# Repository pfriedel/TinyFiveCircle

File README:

Requirements:

1) 5 RGB LEDs - I'm using common anode, but it'll work with common cathode.
   Just differently.  You'll have to map out the pins and colors differently.

2) ATtiny85

3) PCB from OSHpark.  I'm working on a kit.

BOM: (prices are volatile)

1x MCU: http://www.dipmicro.com/store/ATTINY85-20PU ($1.56)
4x 10mm RGB Common Anode LEDs: http://www.dipmicro.com/store/LED10AD ($2)
1x 3xAA Battery holder: http://www.dipmicro.com/store/BH2465 ($3.21)
4x resistors - mine are 1ohm! But 47 is probably more reasonable

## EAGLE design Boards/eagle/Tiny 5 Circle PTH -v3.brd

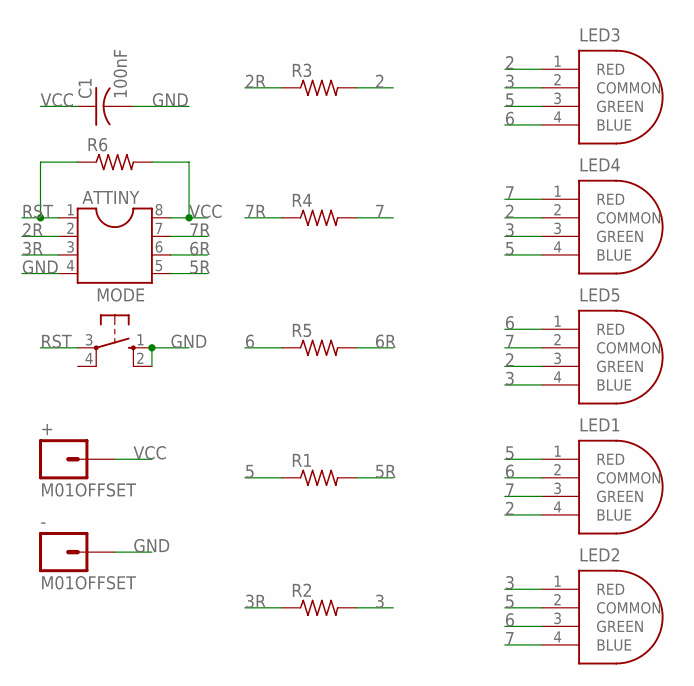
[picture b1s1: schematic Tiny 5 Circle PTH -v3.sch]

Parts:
+: M01OFFSET; 1X01_OFFSET
-: M01OFFSET; 1X01_OFFSET
ATTINY: DIL8S; SOCKET-08
C1: 100nF; C025-025X050
LED1, LED2, LED3, LED4, LED5: 10MM-RGB-LEDACTIVELYUSED; 10MM-RGB-LED-IN-USE
MODE: 10-XX; B3F-10XX
R1, R2, R3, R4, R5: R-US_0207/7; 0207/7
R6: R-US_0207/2V; 0207/2V

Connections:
2: LED1.4 (BLUE), LED3.1 (RED), LED4.2 (COMMON), LED5.3 (GREEN), R3.2
2R: ATTINY.2, R3.1
3: LED2.1 (RED), LED3.2 (COMMON), LED4.3 (GREEN), LED5.4 (BLUE), R2.2
3R: ATTINY.3, R2.1
5: LED1.1 (RED), LED2.2 (COMMON), LED3.3 (GREEN), LED4.4 (BLUE), R1.1
5R: ATTINY.5, R1.2
6: LED1.2 (COMMON), LED2.3 (GREEN), LED3.4 (BLUE), LED5.1 (RED), R5.1
6R: ATTINY.6, R5.2
7: LED1.3 (GREEN), LED2.4 (BLUE), LED4.1 (RED), LED5.2 (COMMON), R4.2
7R: ATTINY.7, R4.1
GND: -.1, ATTINY.4, C1.2, MODE.1 (S), MODE.2 (S1)
RST: ATTINY.1, MODE.3, R6.1
VCC: +.1, ATTINY.8, C1.1, R6.2

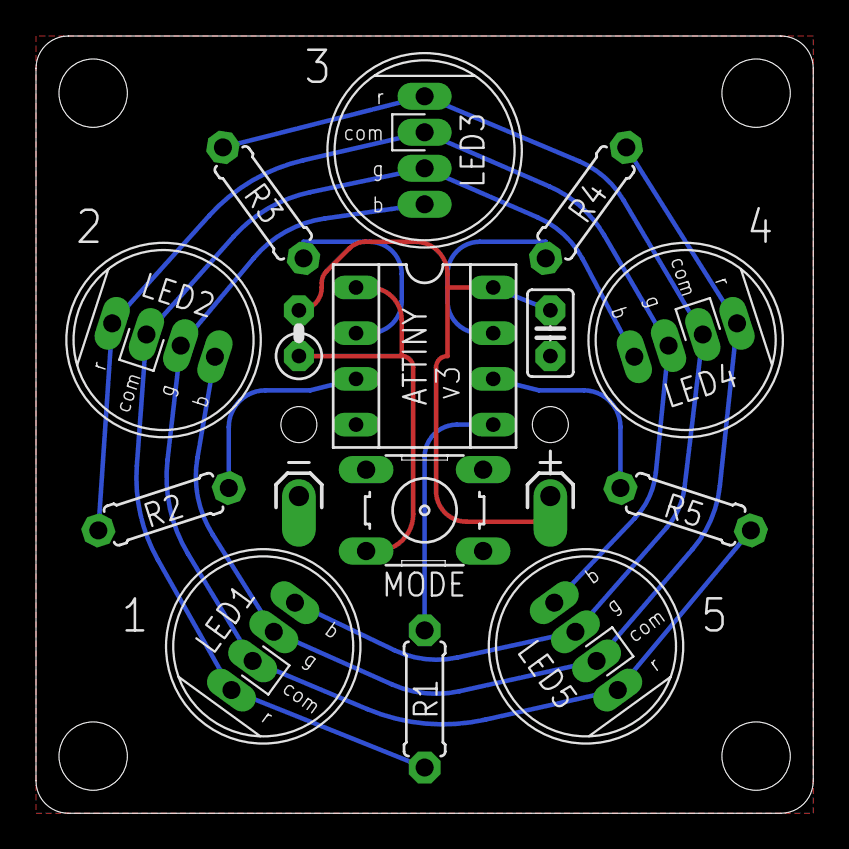
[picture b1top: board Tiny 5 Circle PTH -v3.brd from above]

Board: 2 copper layers, 43.2 x 43.2 mm, 16 parts (0 on the bottom side), 13 nets.

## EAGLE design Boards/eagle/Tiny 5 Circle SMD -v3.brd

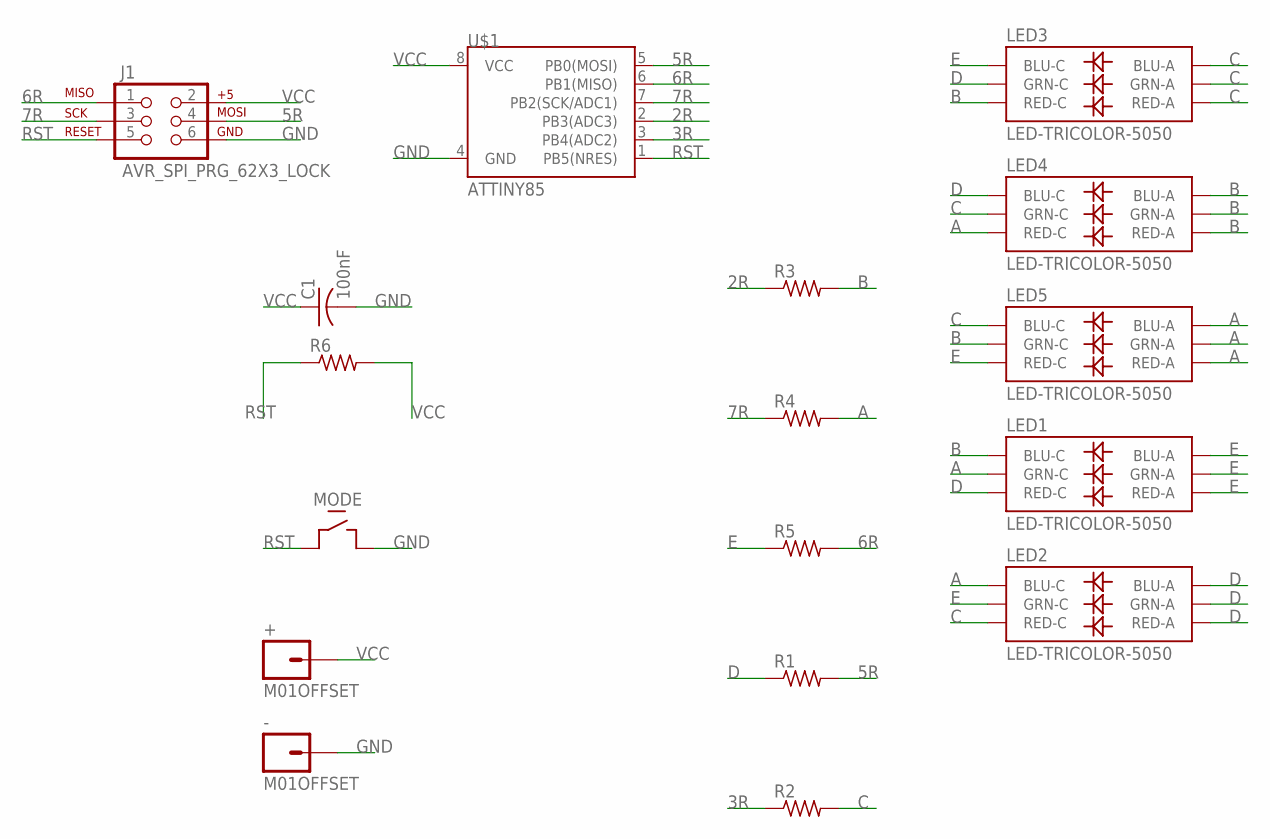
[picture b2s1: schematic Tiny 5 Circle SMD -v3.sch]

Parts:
+: M01OFFSET; 1X01_OFFSET
-: M01OFFSET; 1X01_OFFSET
C1: 100nF; C025-025X050
J1: AVR_SPI_PRG_62X3_LOCK; 2X3_LOCK
LED1, LED2, LED3, LED4, LED5: LED-TRICOLOR-5050
MODE: 3X6MM_SWITCH; 6X3MM-TACT
R1, R2, R3, R4, R5, R6: R-US_M0805; M0805
U$1: ATTINY85; SO08-EIAJ

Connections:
2R: R3.1, U$1.2 (PB3(ADC3))
3R: R2.1, U$1.3 (PB4(ADC2))
5R: J1.4, R1.2, U$1.5 (PB0(MOSI))
6R: J1.1, R5.2, U$1.6 (PB1(MISO))
7R: J1.3, R4.1, U$1.7 (PB2(SCK/ADC1))
A: LED1.4 (GRN-C), LED2.6 (BLU-C), LED4.5 (RED-C), LED5.1 (BLU-A), LED5.2 (RED-A), LED5.3 (GRN-A), R4.2
B: LED1.6 (BLU-C), LED3.5 (RED-C), LED4.1 (BLU-A), LED4.2 (RED-A), LED4.3 (GRN-A), LED5.4 (GRN-C), R3.2
C: LED2.5 (RED-C), LED3.1 (BLU-A), LED3.2 (RED-A), LED3.3 (GRN-A), LED4.4 (GRN-C), LED5.6 (BLU-C), R2.2
D: LED1.5 (RED-C), LED2.1 (BLU-A), LED2.2 (RED-A), LED2.3 (GRN-A), LED3.4 (GRN-C), LED4.6 (BLU-C), R1.1
E: LED1.1 (BLU-A), LED1.2 (RED-A), LED1.3 (GRN-A), LED2.4 (GRN-C), LED3.6 (BLU-C), LED5.5 (RED-C), R5.1
GND: -.1, C1.2, J1.6, MODE.P$2 (OUT), U$1.4 (GND)
RST: J1.5, MODE.P$1 (IN), R6.1, U$1.1 (PB5(NRES))
VCC: +.1, C1.1, J1.2, R6.2, U$1.8 (VCC)

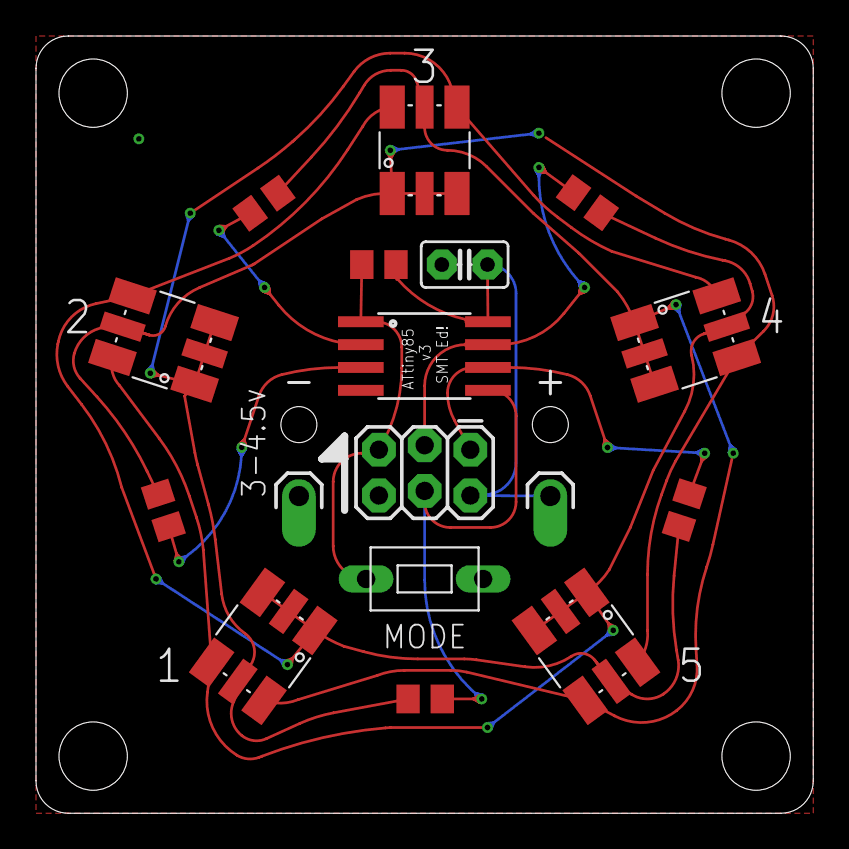
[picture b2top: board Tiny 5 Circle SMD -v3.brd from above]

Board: 2 copper layers, 43.2 x 43.2 mm, 17 parts (0 on the bottom side), 13 nets.

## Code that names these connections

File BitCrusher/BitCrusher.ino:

// Because I tend to forget - the number here is the Port B pin in use.  Pin 5 is PB0, Pin 6 is PB1, etc.
#define LINE_A 0 // PB0 / Pin 5 on ATtiny85 / Pin 14 on an ATmega328 (D8)
#define LINE_B 1 // PB1 / Pin 6 on ATtiny85 / Pin 15 on an ATmega328 (D9)
#define LINE_C 2 // PB2 / Pin 7 on ATtiny85 / Pin 17 on an ATmega328 (D11)
#define LINE_D 3 // PB3 / Pin 2 on ATtiny85 / Pin 18 on an ATmega328 (D12)
#define LINE_E 4 // PB4 / Pin 3 on ATtiny85

#include <avr/power.h>
#include <EEPROM.h>

// How many modes do we want to go through?
#define MAX_MODE 9
// How long should I draw each color on each LED?
#define DRAW_TIME 5

// Location of the brown-out disable switch in the MCU Control Register (MCUCR)
#define BODS 7 
// Location of the Brown-out disable switch enable bit in the MCU Control Register (MCUCR)
#define BODSE 2 

// The base unit for the time comparison. 1000=1s, 10000=10s, 60000=1m, etc.
//#define time_multiplier 1000 
#define time_multiplier 60000
// How many time_multiplier intervals should run before going to sleep?
#define run_time 240

#define MAX_HUE 360 // normalized

// How bit-crushed do you want the bit depth to be?  1 << TIMESCALE is how
// quickly it goes through the LED softpwm scale.

// 1 means 128 shades per color.  3 is 32 colors while 6 is 4 shades per color.
// it sort of scales the time drawing routine, but not well.

// It also affects how bright it it (less time spent drawing nothing) as well as
// the POV flickering rate. Higher numbers are both brighter and less flicker-y.

// the build uses 1 for the PTH versions and 3 for the SMD displays.

#define TIMESCALE 3

byte __attribute__ ((section (".noinit"))) last_mode;

uint8_t led_grid[15] = {
  000 , 000 , 000 , 000 , 000 , // R
  000 , 000 , 000 , 000 , 000 , // G
  000 , 000 , 000 , 000 , 000  // B
};

uint8_t led_grid_next[15] = {
  000 , 000 , 000 , 000 , 000 , // R
  000 , 000 , 000 , 000 , 000 , // G
  000 , 000 , 000 , 000 , 000  // B
};


void setup() {
  Serial.begin(115200);
}

void loop() {
  HueWalk(run_time,millis(),5,1); // 1:1 space to LED, fast progression
}

void HueWalk(uint16_t time, uint32_t start_time, uint8_t width, uint8_t speed) {
  while(1) {
    
    if(millis() >= (start_time + (time * time_multiplier))) { break; }

    for(int16_t colorshift=MAX_HUE; colorshift>0; colorshift = colorshift - speed) {

      if(millis() >= (start_time + (time * time_multiplier))) { break; }
      for(uint8_t led = 0; led<5; led++) {
	//	if(led == 0) { Serial.println(colorshift); }

	uint16_t hue = ((led) * MAX_HUE/(width)+colorshift)%MAX_HUE;
	setLedColorHSV(led, hue, 255, 255);
      }
      draw_for_time(DRAW_TIME); // this gets called 5 times, once per LED.
    }
  }
}


const byte dim_curve[] = {
  0,   1,   1,   2,   2,   2,   2,   2,   2,   3,   3,   3,   3,   3,   3,   3,
  3,   3,   3,   3,   3,   3,   3,   4,   4,   4,   4,   4,   4,   4,   4,   4,
  4,   4,   4,   5,   5,   5,   5,   5,   5,   5,   5,   5,   5,   6,   6,   6,
  6,   6,   6,   6,   6,   7,   7,   7,   7,   7,   7,   7,   8,   8,   8,   8,
  8,   8,   9,   9,   9,   9,   9,   9,   10,  10,  10,  10,  10,  11,  11,  11,
  11,  11,  12,  12,  12,  12,  12,  13,  13,  13,  13,  14,  14,  14,  14,  15,
  15,  15,  16,  16,  16,  16,  17,  17,  17,  18,  18,  18,  19,  19,  19,  20,
  20,  20,  21,  21,  22,  22,  22,  23,  23,  24,  24,  25,  25,  25,  26,  26,
  27,  27,  28,  28,  29,  29,  30,  30,  31,  32,  32,  33,  33,  34,  35,  35,
  36,  36,  37,  38,  38,  39,  40,  40,  41,  42,  43,  43,  44,  45,  46,  47,
  48,  48,  49,  50,  51,  52,  53,  54,  55,  56,  57,  58,  59,  60,  61,  62,
  63,  64,  65,  66,  68,  69,  70,  71,  73,  74,  75,  76,  78,  79,  81,  82,
  83,  85,  86,  88,  90,  91,  93,  94,  96,  98,  99,  101, 103, 105, 107, 109,
  110, 112, 114, 116, 118, 121, 123, 125, 127, 129, 132, 134, 136, 139, 141, 144,
  146, 149, 151, 154, 157, 159, 162, 165, 168, 171, 174, 177, 180, 183, 186, 190,
  193, 196, 200, 203, 207, 211, 214, 218, 222, 226, 230, 234, 238, 242, 248, 255,
};


/*
Inputs:
  p : LED to set
  immediate : Whether the change should go to led_grid or led_grid_next
  hue : 0-360 - color
  sat : 0-255 - how saturated should it be? 0=white, 255=full color
  val : 0-255 - how bright should it be? 0=off, 255=full bright
*/
void setLedColorHSV(uint8_t p, int16_t hue, int16_t sat, int16_t val) {


  /*
    so dim_curve duplicates too many of the low numbers too long, causing the
    animations to look janky.  Maybe 6 2's and 14 3's can be adjusted in other ways.
    
    val = dim_curve[val];
    sat = 255-dim_curve[255-sat];
  */

  while (hue > 360) hue -= 361;
  while (hue < 0) hue += 361;

  int r, g, b, base;

  if (sat == 0) { // Acromatic color (gray). Hue doesn't mind.
    r = g = b = val;
  }
  else {
    base = ((255 - sat) * val)>>8;

    switch(hue/60) {
    case 0:
      r = val;
      g = (((val-base)*hue)/60)+base;
      b = base;
      break;

    case 1:
      r = (((val-base)*(60-(hue%60)))/60)+base;
      g = val;
      b = base;
      break;

    case 2:
      r = base;
      g = val;
      b = (((val-base)*(hue%60))/60)+base;
      break;

    case 3:
      r = base;
      g = (((val-base)*(60-(hue%60)))/60)+base;
      b = val;
      break;

    case 4:
      r = (((val-base)*(hue%60))/60)+base;
      g = base;
      b = val;
      break;

    case 5:
      r = val;
      g = base;
      b = (((val-base)*(60-(hue%60)))/60)+base;
      break;
    }
  }

  // output range is 0-255

  r = r>>TIMESCALE;
  g = g>>TIMESCALE;
  b = b>>TIMESCALE;

  if(p == 0) { 
    Serial.print(hue); 
    Serial.print("  r: "); Serial.print(r);
    Serial.print(" g: "); Serial.print(g);
    Serial.print(" b: "); Serial.println(b);
    
  }


  set_led_rgb(p,r,g,b);
}

/* Args:
   position - 0-4
   red value - 0-255
   green value - 0-255
   blue value - 0-255
*/
void set_led_rgb (uint8_t p, uint8_t r, uint8_t g, uint8_t b) {
  led_grid[p] = r;
  led_grid[p+5] = g;
  led_grid[p+10] = b;
}

// runs draw_frame a supplied number of times.
void draw_for_time(uint16_t time) {
  Serial.print("BEGINNING draw_for_time for ");
  Serial.print(time * (1<<(TIMESCALE-1)));
  Serial.println(" loops.");
  
  for(uint16_t f = 0; f<time * (1 << (TIMESCALE-1)); f++) { 
    draw_frame();   
  }
  Serial.println("ENDING draw_for_time");
  
}

// Anode | cathode
const uint8_t led_dir[15] = {
  ( 1<<LINE_B | 1<<LINE_A ), // 4 r
  ( 1<<LINE_A | 1<<LINE_E ), // 5 r
  ( 1<<LINE_E | 1<<LINE_D ), // 1 r
  ( 1<<LINE_D | 1<<LINE_C ), // 2 r
  ( 1<<LINE_C | 1<<LINE_B ), // 3 r

  ( 1<<LINE_B | 1<<LINE_C ), // 4 g
  ( 1<<LINE_A | 1<<LINE_B ), // 5 g
  ( 1<<LINE_E | 1<<LINE_A ), // 1 g
  ( 1<<LINE_D | 1<<LINE_E ), // 2 g
  ( 1<<LINE_C | 1<<LINE_D ), // 3 g

  ( 1<<LINE_B | 1<<LINE_D ), // 4 b
  ( 1<<LINE_A | 1<<LINE_C ), // 5 b
  ( 1<<LINE_E | 1<<LINE_B ), // 1 b
  ( 1<<LINE_D | 1<<LINE_A ), // 2 b
  ( 1<<LINE_C | 1<<LINE_E ), // 3 b
};

//PORTB output config for each LED (1 = High, 0 = Low)
const uint8_t led_out[15] = {
  ( 1<<LINE_B ), // 4 r
  ( 1<<LINE_A ), // 5 r
  ( 1<<LINE_E ), // 1 r
  ( 1<<LINE_D ), // 2 r
  ( 1<<LINE_C ), // 3 r
  
  ( 1<<LINE_B ), // 4 g
  ( 1<<LINE_A ), // 5 g
  ( 1<<LINE_E ), // 1 g
  ( 1<<LINE_D ), // 2 g
  ( 1<<LINE_C ), // 3 g
  
  ( 1<<LINE_B ), // 4 b
  ( 1<<LINE_A ), // 5 b
  ( 1<<LINE_E ), // 1 b
  ( 1<<LINE_D ), // 2 b
  ( 1<<LINE_C ), // 3 b
};

void light_led(uint8_t led_num) { //led_num must be from 0 to 19
  //DDRD is the ports in use on an ATmega328, DDRB on an ATtiny85
  DDRB = led_dir[led_num];
  PORTB = led_out[led_num];
}

void leds_off() {
  DDRB = 0;
  PORTB = 0;
}

void draw_frame(void){
  uint16_t b;
  uint8_t led;
  // giving the loop a bit of breathing room seems to prevent the last LED from flickering.  Probably optimizes into oblivion anyway.
  for ( led=0; led<=15; led++ ) { 

    for( b=0; b<led_grid[led]; b++) {
      light_led(led);
      if(led == 0) {
	Serial.print(1);
      }
    }
    // and turn the LEDs off for the amount of time in the led_grid array between LED brightness and 255.
    // BUG alert - at timescale 3, 
    // input "68" is 33 total cycles, 9 lit and 24 dark, 
    // input "63" is 32 total cycles, 8 lit and 24 dark.                                                                              
    for( b=led_grid[led]; b < ((1<<(8 - TIMESCALE))-1); b++ ) {
      leds_off();
      if(led == 0) {
	Serial.print(0);
      }
    }
    if(led == 0) {
      Serial.println();
    }
  }
}

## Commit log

2012-09-20 Initial Checkin
2012-09-25 Attempting to use MCUSR for power state management
2012-09-25 Functional MCUSR using EXTRF for state management.
2012-09-25 Properly using MCUSR to spare the EEPROM.
2012-09-26 Prematurely removed the mode decrement in the last checkin.
2012-09-26 Well, that would explain why the 5th LED kept running out of sequence.
2012-09-26 Converted to integer code, regained about 17% of flash in the process.
    I think it looks a bit nicer, too - the brightness doesn't jump around
    so much.
2012-09-27 Major cleanup and functional validation. It's stable again with 2 different HSB to RGB functions.
2012-09-28 Mode cleanup and simplification and dropping the non-normalized color conversion.
    Binary sketch size: 3,688 bytes (of a 8,192 byte maximum)
2012-09-28 Stylistic cleanup
    Binary sketch size: 3,574 bytes (of a 8,192 byte maximum)
2012-09-28 Further map/constrain purging. Major code shrinkage!
    Binary sketch size: 2,808 bytes (of a 8,192 byte maximum)
2012-09-29 Very preliminary larson scanner support.
    Binary sketch size: 3,140 bytes (of a 8,192 byte maximum)
2012-09-29 Monkeying around trying to put the drawing routine in the ISR.
    I suspect it already _is_ using the ISR, but the ISR is firing too
    often and it's stepping all over itself servicing the ISR instead of
    running anything else.
2012-10-04 All new random mode at position 10!
    Binary sketch size: 3,794 bytes (of a 8,192 byte maximum)
2012-10-04 Er yeah. duh. MAX_HUE is > 255, isn't it.
2012-10-05 Tracking down an annoying failure to sleep inside LarsonScanner().
    Binary sketch size: 3,828 bytes (of a 8,192 byte maximum)
2012-10-06 Still wrangling with the Larson Scanner's lack of willingness to sleep.
    Binary sketch size: 3,788 bytes (of a 8,192 byte maximum)
2012-10-08 Switched over to arduino-tiny core.
2012-10-10 Leading toward production board.
2012-10-10 Updating the runtime back to 4 hours
    Binary sketch size: 3,736 bytes (of a 8,192 byte maximum)
2012-10-15 Testing fading frames, but I think the discontinuity between 101 and 200 makes the fader unpredictable.
2012-10-16 Initial checkin - attempting to test more HSV to RGB functions.
2012-10-16 Forgot to note that c2 maps HSL space and not HSV space.
2012-10-16 cleanup
2012-10-16 Swapped to the more accurate HSV to RGB routine, made all the other required timing changes to account for the smaller hue space as well.
2012-10-16 Cope with unbounded hues better.
2012-10-16 Added fading function to larson scanner - looks nice.
    Binary sketch size: 3,918 bytes (of a 8,192 byte maximum)
    (The downside is I think I run up against perceptual issues at
    particular hues where 255 is significantly (redder/greener/bluer) than
    the trail is.)
2012-11-19 Revision 2 board
    Aside from some documentation changes (LED positions & etc), the major
    changes are the LED footprints, the addition of a reset pullup and a
    100nF cap on the power lines.
2012-11-19 Updated comments
2012-11-19 Current revision hex files
2012-11-19 Adjusting modes for the shipping release
    Binary sketch size: 3,458 bytes (of a 8,192 byte maximum)
2012-11-19 Updating fuses for 2.7v BOD instead of no BOD.
2012-11-19 Board management
2012-11-19 And turning off BOD again - it killed the sleep power consumption.
2012-11-20 Ignoring my testing code
2012-11-25 Documentation!
2013-01-16 Changing color depth from 8-bit (ish) to 6-bit.
    This improves PWM duty cycle (brighter!) and reduces that very edge of
    flicker it had been exhibiting with clear lensed LEDs like the surface
    mount kit uses.
2013-01-19 Ignoring the original size image version of the instructions
2013-01-19 Now with feedback from the initial user builds
2013-01-19 Bit crushing in the SoftPWM is better than in the HSV conversion.
    Same effect on both timing and brightness, but it's less prone to
    visible blockness.
2013-01-24 Committing the compiled code.
2013-01-24 Renaming the precompiled versions to differentiate them
    -SMD is bit crushed to 32 shades while the base is still 128 shades per
    color.
2013-01-24 Eagle board and schematic snapshots
2013-01-24 I always forget how this is defined
    and I hate figuring it out empirically.
2013-01-25 Experiments in bit crushing.
2013-01-25 Refactored the bit crushing.
    Again. I know. But the BitCrusher script made it clear I was doing it
    less optimally.
2013-01-25 Updated revision of the precompiled code.
2013-01-25 And a new PTH version
2013-01-26 Correcting a little unintentional misdirection in the comments
    1 was originally at the 12 o'clock position. Changing the order of the
    array changes where the "gap" is in several modes.
2013-01-26 A stub for testing new modes on a serial equipped board
2013-01-26 RandHueWalk tested and working.
    MultiPrimary is kind of not doing what I want it to do in this build.
    Might not even really be possible, but banging against it I have a
    better idea now. Maybe.
2013-01-27 Bug fix in the hue correction - 360->0 sparkles, 359->0 doesn't.
2013-01-27 Bug fix in the hue correction & additional debugging flags
2013-01-27 BiColorWalk added and tested.
2013-02-02 Implementing the new modes. It's getting a bit hard to keep track.
2013-02-04 New modes
2013-02-05 New modes!
2013-02-12 Corrected a longstanding bug and cleaned up some slightly misleading code.
2013-04-23 Removes PrimaryColors() from AllRand() and increases depth to 2 for more soothing strips.
2013-12-08 Never committed the boards to the repository, whoops!
2013-12-19 Finally licensing it

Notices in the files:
parts and their libraries:
SparkFun: Licensing: CC v3.0 Share-Alike You are welcome to use this library for commercial purposes.
